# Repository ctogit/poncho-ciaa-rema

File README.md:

# poncho-ciaa-rema
Desarrollo de placa poncho para placa CIAA-NXP en el marco del proyecto de reacondicionamiento electrónico del telemanipulador cartesiano "REMA".

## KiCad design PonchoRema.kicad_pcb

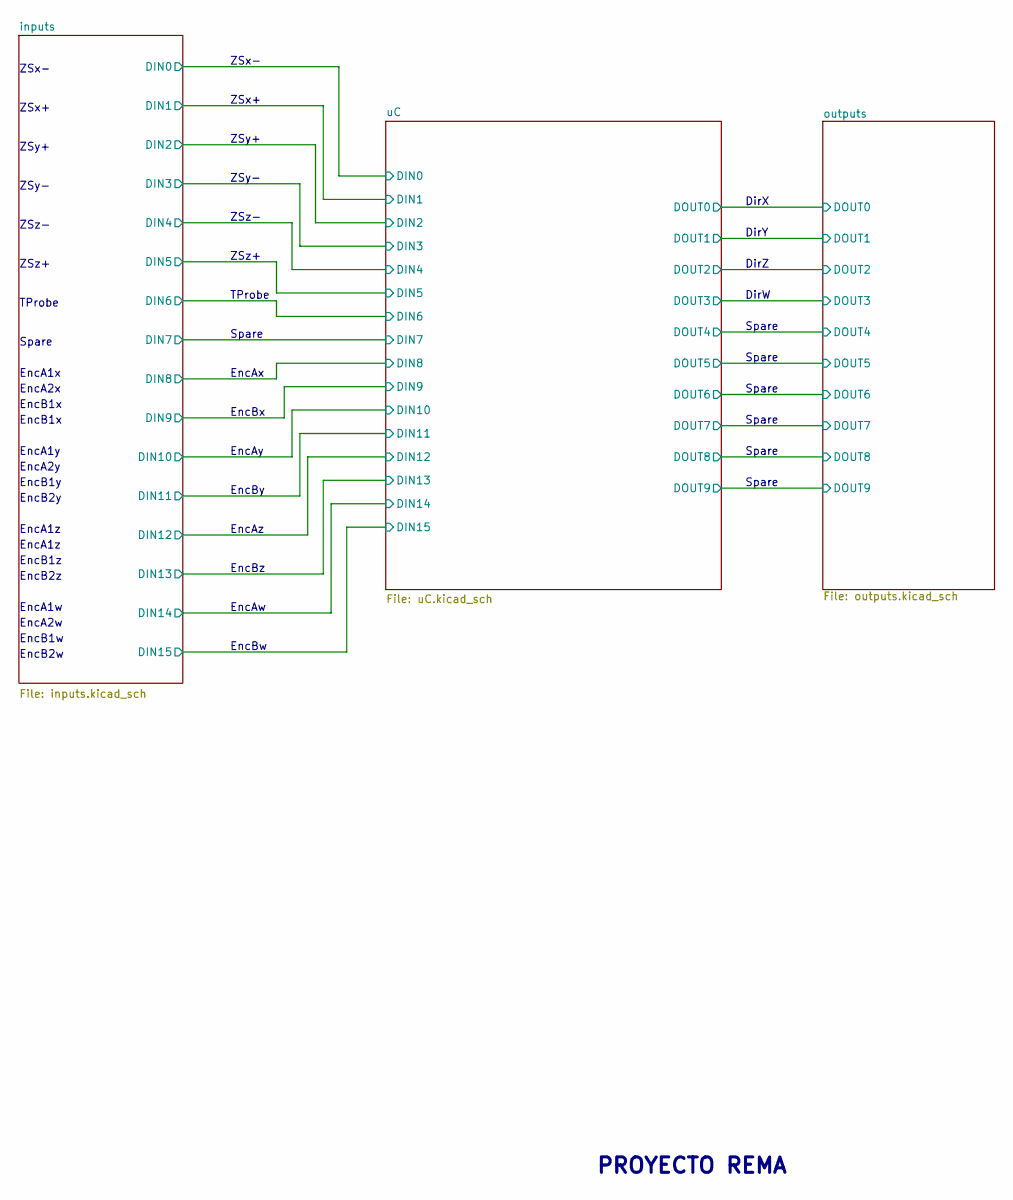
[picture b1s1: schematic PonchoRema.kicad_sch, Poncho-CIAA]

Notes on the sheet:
ZSx+
ZSz+
EncB1y
Spare
EncAy
EncAw
EncBz
ZSx-
EncB2y
EncA2y
TProbe
ZSy+
EncA1w
EncBx
EncB2z
ZSy-
EncB1x
EncB2w
EncB1z
EncA1z
EncBw
ZSz-
EncA2w
DirW
EncBy
EncAz
EncA1y
EncA2x
DirZ
DirY
EncAx
EncB1w
PROYECTO REMA
EncA1x
DirX

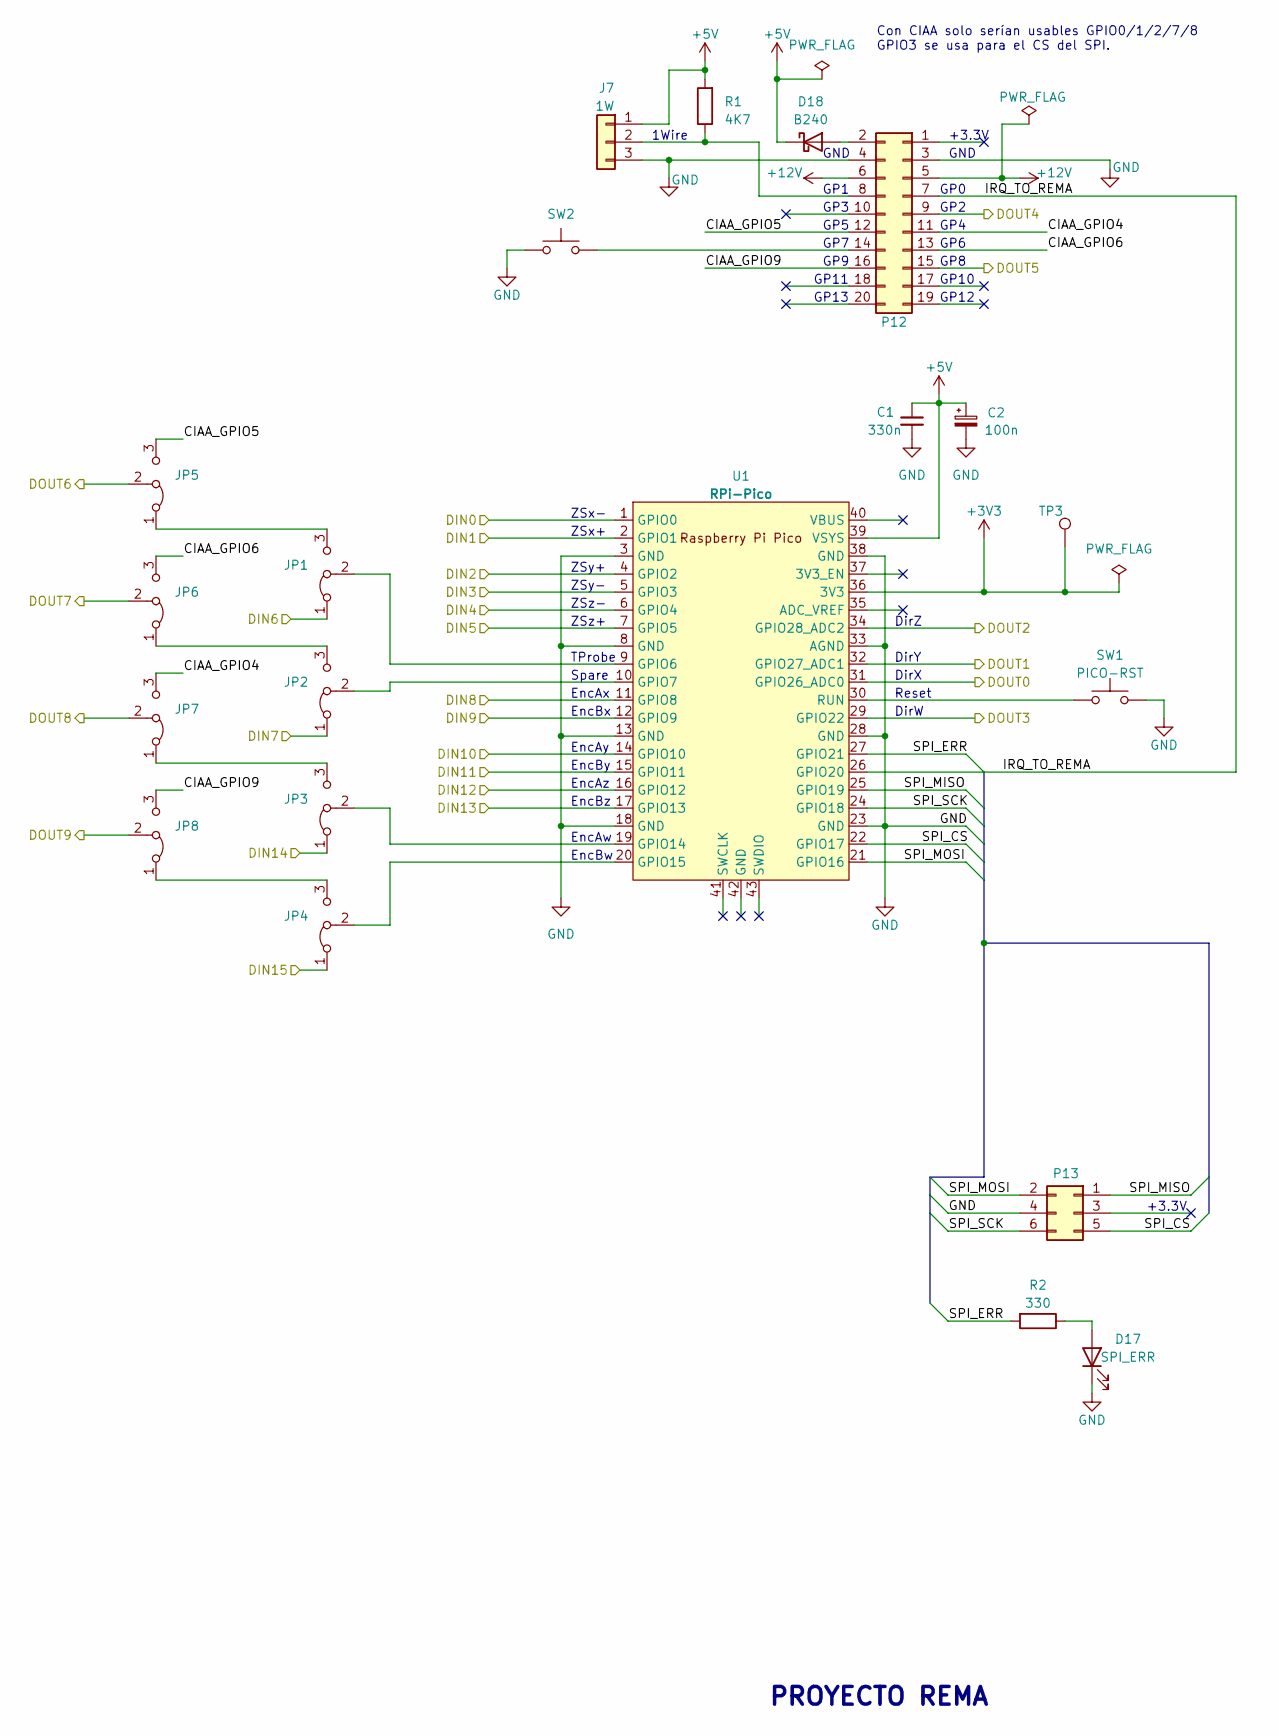
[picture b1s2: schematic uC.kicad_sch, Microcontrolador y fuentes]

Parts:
C1: 330n; C_1206_3216Metric
C2: 100n; C_1206_3216Metric
D17: SPI_ERR; LED_1206_3216Metric
D18: B240; D_SMB
J7: 1W; PinHeader_1x03_P2.54mm_Vertical
JP1, JP2, JP3, JP4, JP5, JP6, JP7, JP8: Jumper_3_Bridged12; PinHeader_1x03_P2.54mm_Vertical
P12: Conn_02x10_Odd_Even; PinHeader_2x10_P2.54mm_Vertical
P13: PinHeader_2x03_P2.54mm_Vertical
R1: 4K7; R_Axial_DIN0207_L6.3mm_D2.5mm_P7.62mm_Horizontal
R2: 330; R_1206_3216Metric
SW1: PICO-RST; SW_PUSH_6mm
SW2: SW_Push; SW_PUSH_6mm
TP3: TestPoint; TestPoint_Pad_D2.0mm
U1: RPi-Pico; RPi_Pico_SMD_TH

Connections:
+3V3: TP3.1, U1.36 (3V3)
+5V: C1.1, C2.1, D18.1 (K), J7.1, R1.2, U1.39 (VSYS); also elsewhere on the board
/inputs/DIN0: U1.1 (GPIO0); also elsewhere on the board
/inputs/DIN1: U1.2 (GPIO1); also elsewhere on the board
/inputs/DIN2: U1.4 (GPIO2); also elsewhere on the board
/inputs/DIN3: U1.5 (GPIO3); also elsewhere on the board
/inputs/DIN4: U1.6 (GPIO4); also elsewhere on the board
/inputs/DIN5: U1.7 (GPIO5); also elsewhere on the board
/inputs/DIN6: JP1.1 (A); also elsewhere on the board
/inputs/DIN7: JP2.1 (A); also elsewhere on the board
/inputs/DIN8: U1.11 (GPIO8); also elsewhere on the board
/inputs/DIN9: U1.12 (GPIO9); also elsewhere on the board
/inputs/DIN10: U1.14 (GPIO10); also elsewhere on the board
/inputs/DIN11: U1.15 (GPIO11); also elsewhere on the board
/inputs/DIN12: U1.16 (GPIO12); also elsewhere on the board
/inputs/DIN13: U1.17 (GPIO13); also elsewhere on the board
/inputs/DIN14: JP3.1 (A); also elsewhere on the board
/inputs/DIN15: JP4.1 (A); also elsewhere on the board
/outputs/DOUT0: U1.31 (GPIO26_ADC0); also elsewhere on the board
/outputs/DOUT1: U1.32 (GPIO27_ADC1); also elsewhere on the board
/outputs/DOUT2: U1.34 (GPIO28_ADC2); also elsewhere on the board
/outputs/DOUT3: U1.29 (GPIO22); also elsewhere on the board
/outputs/DOUT6: JP5.2 (C); also elsewhere on the board
/outputs/DOUT7: JP6.2 (C); also elsewhere on the board
/outputs/DOUT8: JP7.2 (C); also elsewhere on the board
/outputs/DOUT9: JP8.2 (C); also elsewhere on the board
/uC/CIAA_GPIO4: JP7.3 (B); also elsewhere on the board
/uC/CIAA_GPIO5: JP5.3 (B); also elsewhere on the board
/uC/CIAA_GPIO6: JP6.3 (B); also elsewhere on the board
/uC/CIAA_GPIO9: JP8.3 (B); also elsewhere on the board
/uC/IRQ_TO_REMA: U1.26 (GPIO20); also elsewhere on the board
/uC/SPI_CS: U1.22 (GPIO17); also elsewhere on the board
/uC/SPI_ERR: R2.2, U1.27 (GPIO21)
/uC/SPI_MISO: U1.25 (GPIO19); also elsewhere on the board
/uC/SPI_MOSI: U1.21 (GPIO16); also elsewhere on the board
/uC/SPI_SCK: U1.24 (GPIO18); also elsewhere on the board
GND: C1.2, C2.2, D17.1 (K), J7.3, SW1.2, SW2.1, U1.3 (GND), U1.8 (GND), U1.13 (GND), U1.18 (GND), U1.23 (GND), U1.28 (GND), U1.33 (AGND), U1.38 (GND); also elsewhere on the board
unnamed: D17.2 (A), R2.1
unnamed 84: D18.2 (A); also elsewhere on the board
unnamed 119: J7.2, R1.1; also elsewhere on the board
unnamed: JP1.3 (B), JP5.1 (A)
unnamed: JP1.2 (C), U1.9 (GPIO6)
unnamed: JP2.3 (B), JP6.1 (A)
unnamed: JP2.2 (C), U1.10 (GPIO7)
unnamed: JP3.3 (B), JP7.1 (A)
unnamed: JP3.2 (C), U1.19 (GPIO14)
unnamed: JP4.3 (B), JP8.1 (A)
unnamed: JP4.2 (C), U1.20 (GPIO15)
unnamed 130: SW2.2; also elsewhere on the board
unnamed: SW1.1, U1.30 (RUN)

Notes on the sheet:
GND
GP12
DirW
1Wire
ZSx-
GP1
ZSy-
ZSz-
GP6
EncAz
Con CIAA solo serían usables GPIO0/1/2/7/8 GPIO3 se usa para el CS del SPI.
Reset
GP13
GP8
EncBy
EncBz
ZSz+
DirX
GP2
EncBx
GP7
GP11
Spare
TProbe
GP9
EncAx
DirY
ZSx+
GP5
+3.3V
EncAy
GP3
ZSy+
GP10
EncAw
GP4
EncBw
GP0
PROYECTO REMA
DirZ

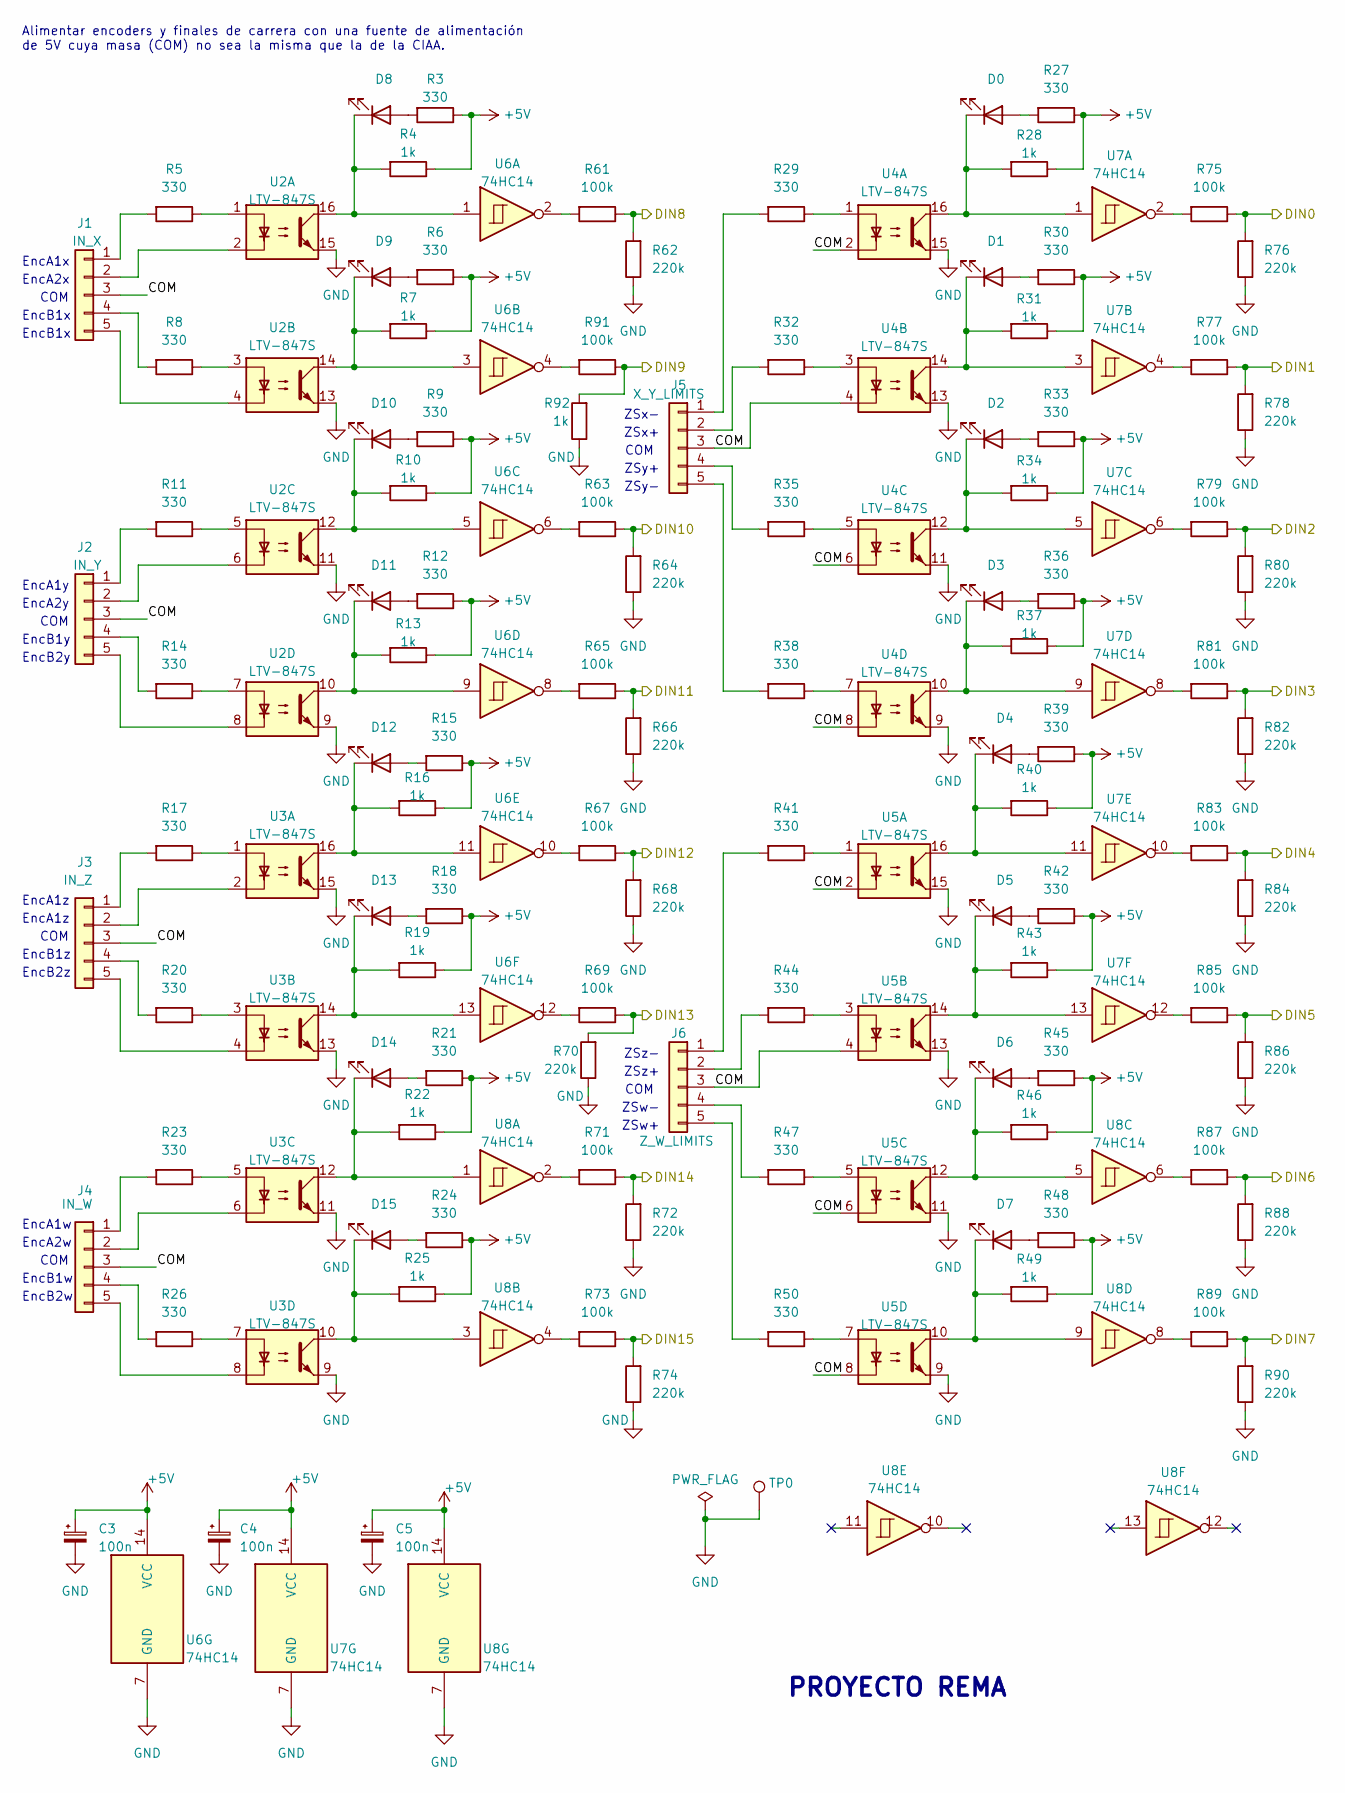
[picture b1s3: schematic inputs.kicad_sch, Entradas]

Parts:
C3, C4, C5: 100n; C_1206_3216Metric
D0, D1, D2, D3, D4, D5, D6, D7, D8, D9, D10, D11, D12, D13, D14, D15: LedGreen; LED_1206_3216Metric
J1: IN_X; PinHeader_1x05_P2.54mm_Vertical
J2: IN_Y; PinHeader_1x05_P2.54mm_Vertical
J3: IN_Z; PinHeader_1x05_P2.54mm_Vertical
J4: IN_W; PinHeader_1x05_P2.54mm_Vertical
J5: X_Y_LIMITS; PinHeader_1x05_P2.54mm_Vertical
J6: Z_W_LIMITS; PinHeader_1x05_P2.54mm_Vertical
R3, R5, R6, R8, R9, R11, R12, R14, R15, R17, R18, R20, R21, R23, R24, R26, R27, R29, R30, R32, R33, R35, R36, R38, R39, R41, R42, R44, R45, R47, R48, R50: 330; R_1206_3216Metric
R4, R7, R10, R13, R16, R19, R22, R25, R28, R31, R34, R37, R40, R43, R46, R49, R92: 1k; R_1206_3216Metric
R61, R63, R65, R67, R69, R71, R73, R75, R77, R79, R81, R83, R85, R87, R89, R91: 100k; R_1206_3216Metric
R62, R64, R66, R68, R70, R72, R74, R76, R78, R80, R82, R84, R86, R88, R90: 220k; R_1206_3216Metric
TP0: TestPoint; TestPoint_Pad_D2.0mm
U2, U3, U4, U5: LTV-847S; DIP-16_W7.62mm_LongPads
U6, U7, U8: 74HC14; SOIC-14_3.9x8.7mm_P1.27mm

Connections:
+5V: C3.1, C4.1, C5.1, R3.1, R4.1, R6.1, R7.1, R9.1, R10.1, R12.1, R13.1, R15.1, R16.1, R18.1, R19.1, R21.1, R22.1, R24.1, R25.1, R27.1, R28.1, R30.1, R31.1, R33.1, R34.1, R36.1, R37.1, R39.1, R40.1, R42.1, R43.1, R45.1, R46.1, R48.1, R49.1, U6.14 (VCC), U7.14 (VCC), U8.14 (VCC); also elsewhere on the board
/inputs/COM: J1.3, J2.3, J3.3, J4.3, J5.3, J6.3, U4.2, U4.4, U4.6, U4.8, U5.2, U5.4, U5.6, U5.8
/inputs/DIN0: R75.1, R76.2; also elsewhere on the board
/inputs/DIN1: R77.1, R78.2; also elsewhere on the board
/inputs/DIN2: R79.1, R80.2; also elsewhere on the board
/inputs/DIN3: R81.1, R82.2; also elsewhere on the board
/inputs/DIN4: R83.1, R84.2; also elsewhere on the board
/inputs/DIN5: R85.1, R86.2; also elsewhere on the board
/inputs/DIN6: R87.1, R88.2; also elsewhere on the board
/inputs/DIN7: R89.1, R90.2; also elsewhere on the board
/inputs/DIN8: R61.1, R62.2; also elsewhere on the board
/inputs/DIN9: R91.1, R92.2; also elsewhere on the board
/inputs/DIN10: R63.1, R64.2; also elsewhere on the board
/inputs/DIN11: R65.1, R66.2; also elsewhere on the board
/inputs/DIN12: R67.1, R68.2; also elsewhere on the board
/inputs/DIN13: R69.1, R70.2; also elsewhere on the board
/inputs/DIN14: R71.1, R72.2; also elsewhere on the board
/inputs/DIN15: R73.1, R74.2; also elsewhere on the board
GND: C3.2, C4.2, C5.2, R62.1, R64.1, R66.1, R68.1, R70.1, R72.1, R74.1, R76.1, R78.1, R80.1, R82.1, R84.1, R86.1, R88.1, R90.1, R92.1, TP0.1, U2.9, U2.11, U2.13, U2.15, U3.9, U3.11, U3.13, U3.15, U4.9, U4.11, U4.13, U4.15, U5.9, U5.11, U5.13, U5.15, U6.7 (GND), U7.7 (GND), U8.7 (GND); also elsewhere on the board
unnamed: D0.2 (A), R27.2
unnamed: D0.1 (K), R28.2, U4.16, U7.1
unnamed: D1.2 (A), R30.2
unnamed: D1.1 (K), R31.2, U4.14, U7.3
unnamed: D2.2 (A), R33.2
unnamed: D2.1 (K), R34.2, U4.12, U7.5
unnamed: D3.2 (A), R36.2
unnamed: D3.1 (K), R37.2, U4.10, U7.9
unnamed: D4.2 (A), R39.2
unnamed: D4.1 (K), R40.2, U5.16, U7.11
unnamed: D5.2 (A), R42.2
unnamed: D5.1 (K), R43.2, U5.14, U7.13
unnamed: D6.2 (A), R45.2
unnamed: D6.1 (K), R46.2, U5.12, U8.5
unnamed: D7.2 (A), R48.2
unnamed: D7.1 (K), R49.2, U5.10, U8.9
unnamed: D8.2 (A), R3.2
unnamed: D8.1 (K), R4.2, U2.16, U6.1
unnamed: D9.2 (A), R6.2
unnamed: D9.1 (K), R7.2, U2.14, U6.3
unnamed: D10.2 (A), R9.2
unnamed: D10.1 (K), R10.2, U2.12, U6.5
unnamed: D11.2 (A), R12.2
unnamed: D11.1 (K), R13.2, U2.10, U6.9
unnamed: D12.2 (A), R15.2
unnamed: D12.1 (K), R16.2, U3.16, U6.11
unnamed: D13.2 (A), R18.2
unnamed: D13.1 (K), R19.2, U3.14, U6.13
unnamed: D14.2 (A), R21.2
unnamed: D14.1 (K), R22.2, U3.12, U8.1
unnamed: D15.2 (A), R24.2
unnamed: D15.1 (K), R25.2, U3.10, U8.3
unnamed: J1.1, R5.2
unnamed: J1.2, U2.2
unnamed: J1.4, R8.2
unnamed: J1.5, U2.4
unnamed: J2.1, R11.2
unnamed: J2.2, U2.6
unnamed: J2.4, R14.2
unnamed: J2.5, U2.8
unnamed: J3.1, R17.2
unnamed: J3.2, U3.2
unnamed: J3.4, R20.2
unnamed: J3.5, U3.4
unnamed: J4.1, R23.2
unnamed: J4.2, U3.6
unnamed: J4.4, R26.2
unnamed: J4.5, U3.8
unnamed: J5.1, R29.2
unnamed: J5.2, R32.2
unnamed: J5.4, R35.2
unnamed: J5.5, R38.2
unnamed: J6.1, R41.2
unnamed: J6.2, R44.2
unnamed: J6.4, R47.2
unnamed: J6.5, R50.2
unnamed: R5.1, U2.1
unnamed: R8.1, U2.3
unnamed: R11.1, U2.5
unnamed: R14.1, U2.7
unnamed: R17.1, U3.1
unnamed: R20.1, U3.3
unnamed: R23.1, U3.5
unnamed: R26.1, U3.7
unnamed: R29.1, U4.1
unnamed: R32.1, U4.3
unnamed: R35.1, U4.5
unnamed: R38.1, U4.7
unnamed: R41.1, U5.1
unnamed: R44.1, U5.3
unnamed: R47.1, U5.5
unnamed: R50.1, U5.7
unnamed: R61.2, U6.2
unnamed: R63.2, U6.6
unnamed: R65.2, U6.8
unnamed: R67.2, U6.10
unnamed: R69.2, U6.12
unnamed: R71.2, U8.2
unnamed: R73.2, U8.4
unnamed: R75.2, U7.2
unnamed: R77.2, U7.4
unnamed: R79.2, U7.6
unnamed: R81.2, U7.8
unnamed: R83.2, U7.10
unnamed: R85.2, U7.12
unnamed: R87.2, U8.6
unnamed: R89.2, U8.8
unnamed: R91.2, U6.4

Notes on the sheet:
ZSy+
EncA2w
ZSz-
EncA1z
ZSx+
COM
EncB1w
EncA1w
EncB1y
EncA1x
EncB2y
EncA2y
PROYECTO REMA
EncB1z
ZSw-
Alimentar encoders y finales de carrera con una fuente de alimentación de 5V cuya masa (COM) no sea la misma que la de la CIAA.
EncB1x
EncA1y
EncB2z
ZSx-
ZSz+
ZSw+
ZSy-
EncA2x
EncB2w

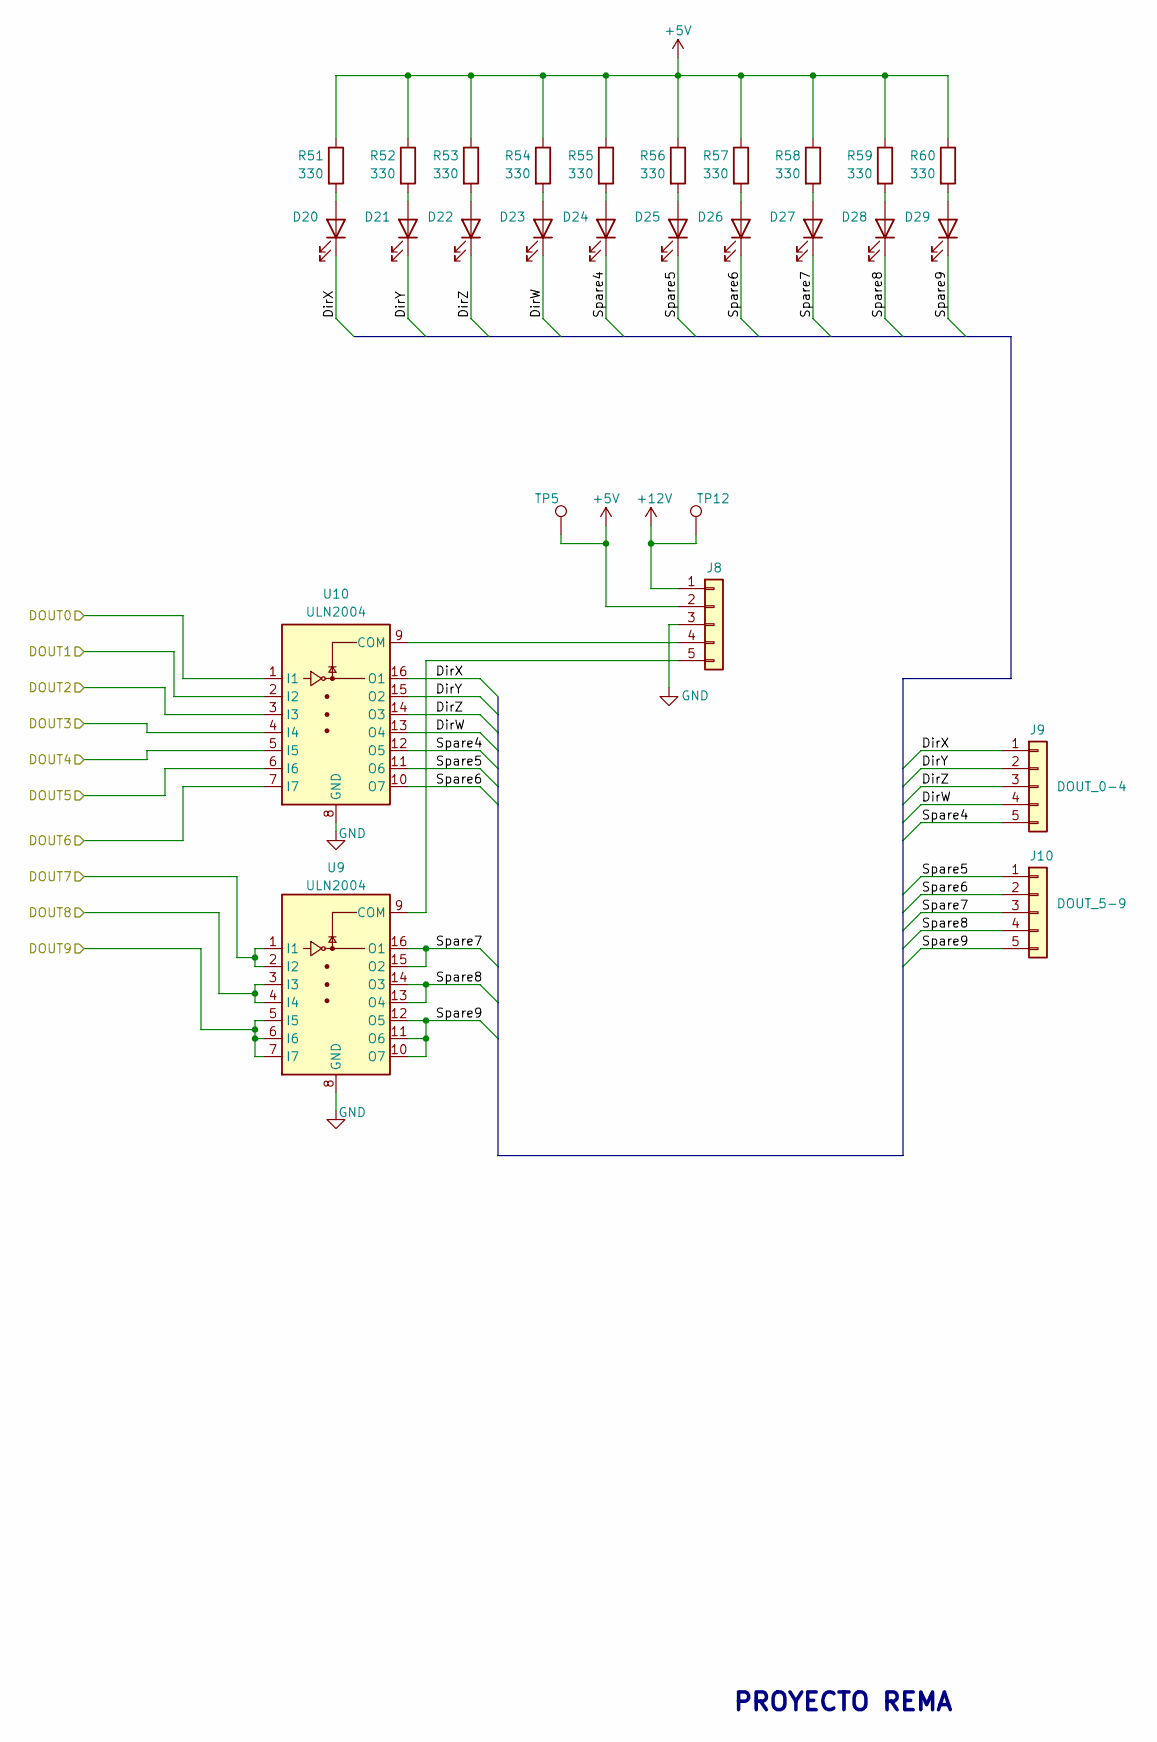
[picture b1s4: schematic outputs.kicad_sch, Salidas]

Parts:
D20, D21, D22, D23, D24, D25, D26, D27, D28, D29: LedRed; LED_1206_3216Metric
J8: Conn_01x05; PinHeader_1x05_P2.54mm_Vertical
J9: DOUT_0-4; PinHeader_1x05_P2.54mm_Vertical
J10: DOUT_5-9; PinHeader_1x05_P2.54mm_Vertical
R51, R52, R53, R54, R55, R56, R57, R58, R59, R60: 330; R_1206_3216Metric
TP5, TP12: TestPoint; TestPoint_Pad_D2.0mm
U9, U10: ULN2004; SO-16_3.9x9.9mm_P1.27mm

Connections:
+5V: J8.2, R51.1, R52.1, R53.1, R54.1, R55.1, R56.1, R57.1, R58.1, R59.1, R60.1, TP5.1; also elsewhere on the board
+12V: J8.1, TP12.1; also elsewhere on the board
/outputs/DOUT0: U10.1 (I1); also elsewhere on the board
/outputs/DOUT1: U10.2 (I2); also elsewhere on the board
/outputs/DOUT2: U10.3 (I3); also elsewhere on the board
/outputs/DOUT3: U10.4 (I4); also elsewhere on the board
/outputs/DOUT4: U10.5 (I5); also elsewhere on the board
/outputs/DOUT5: U10.6 (I6); also elsewhere on the board
/outputs/DOUT6: U10.7 (I7); also elsewhere on the board
/outputs/DOUT7: U9.1 (I1), U9.2 (I2); also elsewhere on the board
/outputs/DOUT8: U9.3 (I3), U9.4 (I4); also elsewhere on the board
/outputs/DOUT9: U9.5 (I5), U9.6 (I6), U9.7 (I7); also elsewhere on the board
/outputs/DirW: D23.1 (K), J9.4, U10.13 (O4)
/outputs/DirX: D20.1 (K), J9.1, U10.16 (O1)
/outputs/DirY: D21.1 (K), J9.2, U10.15 (O2)
/outputs/DirZ: D22.1 (K), J9.3, U10.14 (O3)
/outputs/Spare4: D24.1 (K), J9.5, U10.12 (O5)
/outputs/Spare5: D25.1 (K), J10.1, U10.11 (O6)
/outputs/Spare6: D26.1 (K), J10.2, U10.10 (O7)
/outputs/Spare7: D27.1 (K), J10.3, U9.15 (O2), U9.16 (O1)
/outputs/Spare8: D28.1 (K), J10.4, U9.13 (O4), U9.14 (O3)
/outputs/Spare9: D29.1 (K), J10.5, U9.10 (O7), U9.11 (O6), U9.12 (O5)
GND: J8.3, U9.8 (GND), U10.8 (GND); also elsewhere on the board
unnamed: D20.2 (A), R51.2
unnamed: D21.2 (A), R52.2
unnamed: D22.2 (A), R53.2
unnamed: D23.2 (A), R54.2
unnamed: D24.2 (A), R55.2
unnamed: D25.2 (A), R56.2
unnamed: D26.2 (A), R57.2
unnamed: D27.2 (A), R58.2
unnamed: D28.2 (A), R59.2
unnamed: D29.2 (A), R60.2
unnamed: J8.4, U10.9 (COM)
unnamed: J8.5, U9.9 (COM)

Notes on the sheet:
PROYECTO REMA

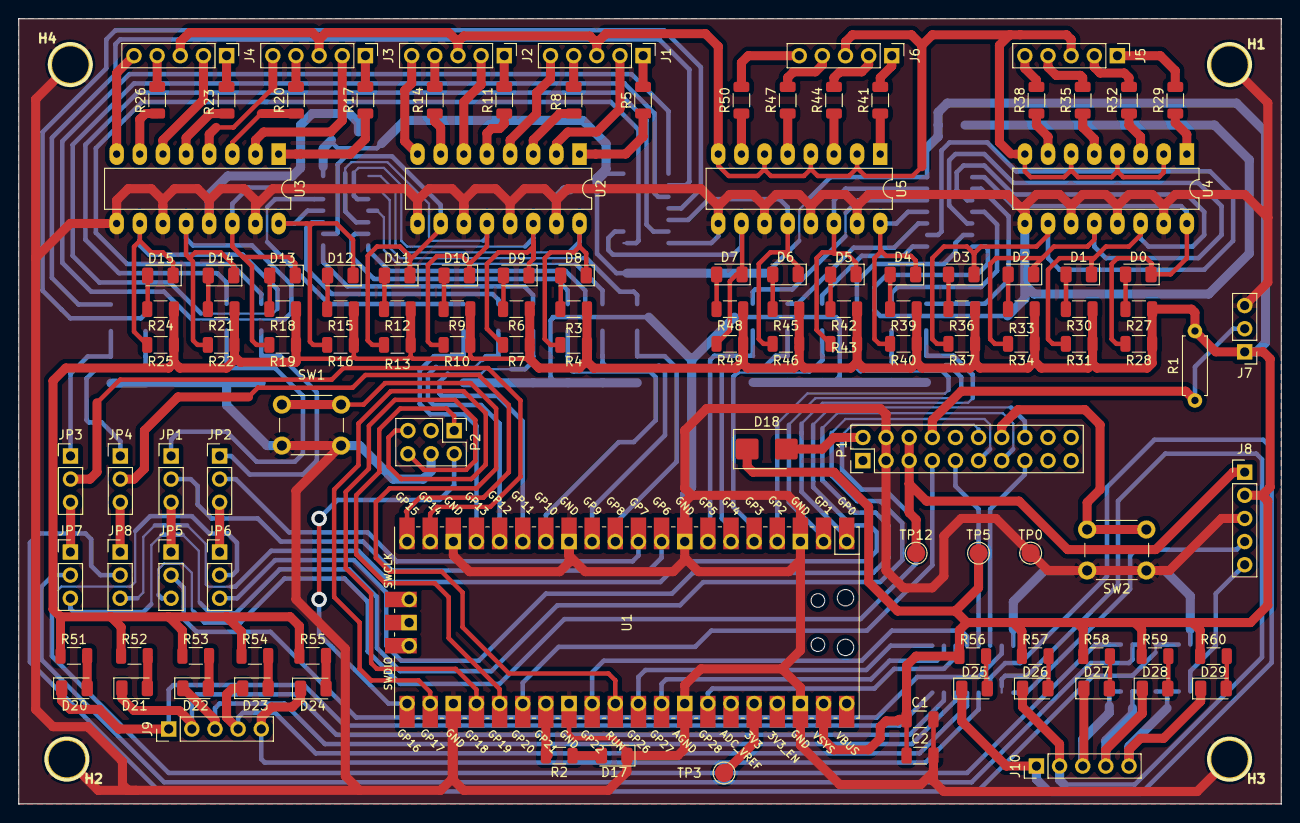
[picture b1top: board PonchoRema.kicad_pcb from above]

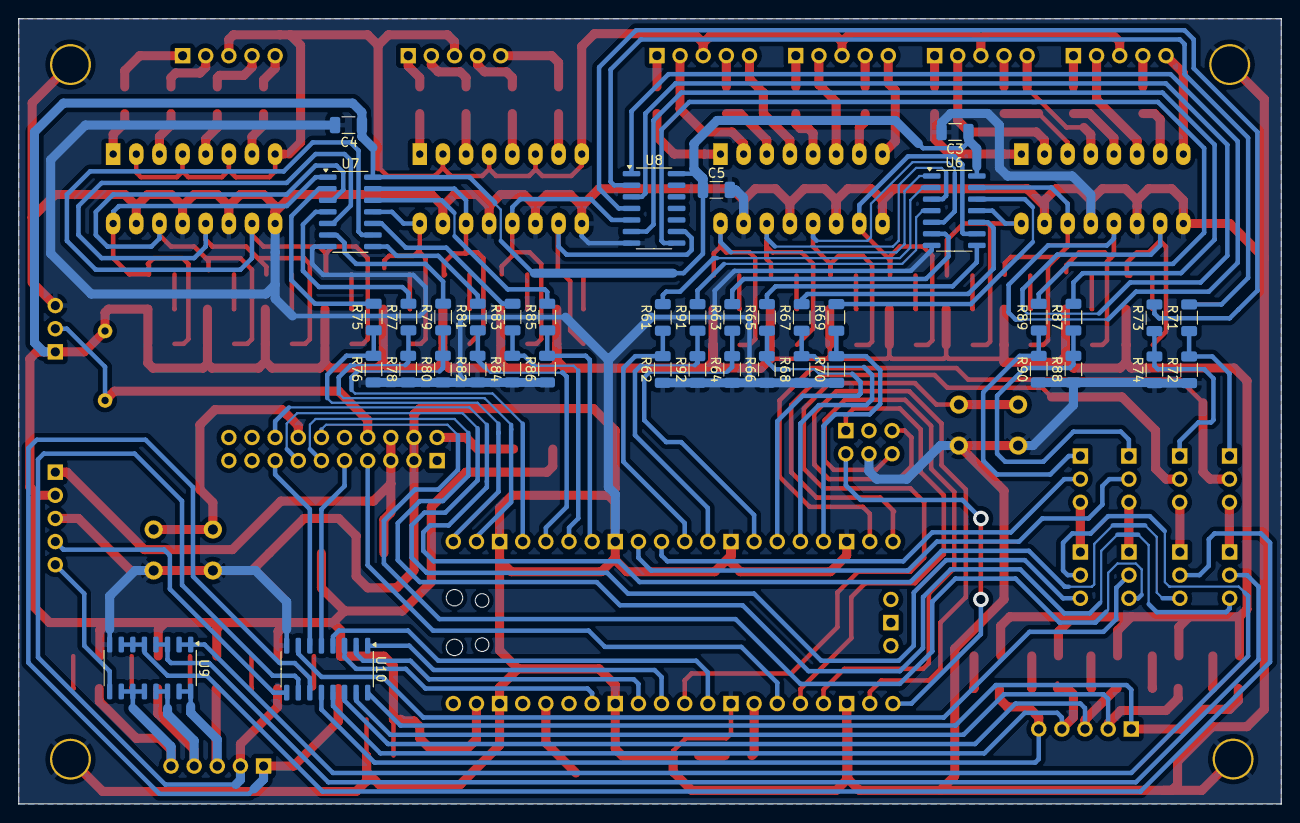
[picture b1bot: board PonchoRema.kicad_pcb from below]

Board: 2 copper layers, 138.6 x 86.2 mm, 165 parts (40 on the bottom side), 164 nets.

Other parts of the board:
H1, H2, H3, H4: 4mm; 1pin
P1: Conn_02x10_Odd_Even; PinHeader_2x10_P2.54mm_Vertical
P2: PinHeader_2x03_P2.54mm_Vertical

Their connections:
+12V: P1.5, P1.6; also elsewhere on the board
/outputs/DOUT4: P1.9; also elsewhere on the board
/outputs/DOUT5: P1.15; also elsewhere on the board
/uC/CIAA_GPIO4: P1.11; also elsewhere on the board
/uC/CIAA_GPIO5: P1.12; also elsewhere on the board
/uC/CIAA_GPIO6: P1.13; also elsewhere on the board
/uC/CIAA_GPIO9: P1.16; also elsewhere on the board
/uC/IRQ_TO_REMA: P1.7; also elsewhere on the board
/uC/SPI_CS: P2.5; also elsewhere on the board
/uC/SPI_MISO: P2.1; also elsewhere on the board
/uC/SPI_MOSI: P2.2; also elsewhere on the board
/uC/SPI_SCK: P2.6; also elsewhere on the board
GND: H1.1, H2.1, H3.1, H4.1, P1.3, P1.4, P2.4; also elsewhere on the board
unnamed 84: P1.2; also elsewhere on the board
unnamed 119: P1.8; also elsewhere on the board
unnamed 130: P1.14; also elsewhere on the board

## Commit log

2024-03-25 Circuito esqumático listo, falta ver los footprints de cada componente e iniciar el diseño del pcb
2024-03-26 Avances en corrección de errores en conexiones eléctricas (ERC).
2024-03-26 Se corrigieron errores de conexión. Falta asignar footprints aún
2024-03-27 se agregan jumpers para elegir entre entradas/salidas
2024-03-27 Esquemático listo, sin errores de conexión y con todos los footprints especificados
2024-03-27 Se agrega carpeta que contiene los simbolos, footprints y modelo 3D de la RPi-pico
2024-03-27 Comienza el diseño del pcb
2024-03-28 Avances con el pcb antes de un laaargo finde
2024-04-03 Se agregan divisores resisitivos a la salida de los schmitt triggers para asegurar que no le lleguen 5V a las entradas de la pico. Se acutaliza el pcb y se acomodan los componentes en dos capas
2024-04-03 Comienza ruteo en pcb
2024-04-04 capa top lista, falta capa bottom del pcb
2024-04-05 PCB: Faltan rutear 4 líneas de la capa bottom
2024-04-05 pcb listo, ver detalles
2024-04-06 Placa poncho v1.0 lista para fabricar
2024-04-08 Terminaciones menores y generación de pdf para cotización
2024-04-10 Se reemplaza ULN2004 por ULN2003 ya que este último es compatible con entradas 3V3. Se optimiza el pcb en cuanto a pistas y planos de masa debajo de los ULN.
2024-04-12 Se generan archivos gerber y se procede a fabricar.
